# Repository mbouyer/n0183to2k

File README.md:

# n0183to2k
generic NMEA0183 to N2K gateway

This is a generic NMEA0183 to N2K gateway, derived from my weatherstation 
sensor board. It has a NMEA0183 input, switchable 12v power supply output
and a 3.3v i2c connector for additional sensors (e.g. BME280 or SHT20)

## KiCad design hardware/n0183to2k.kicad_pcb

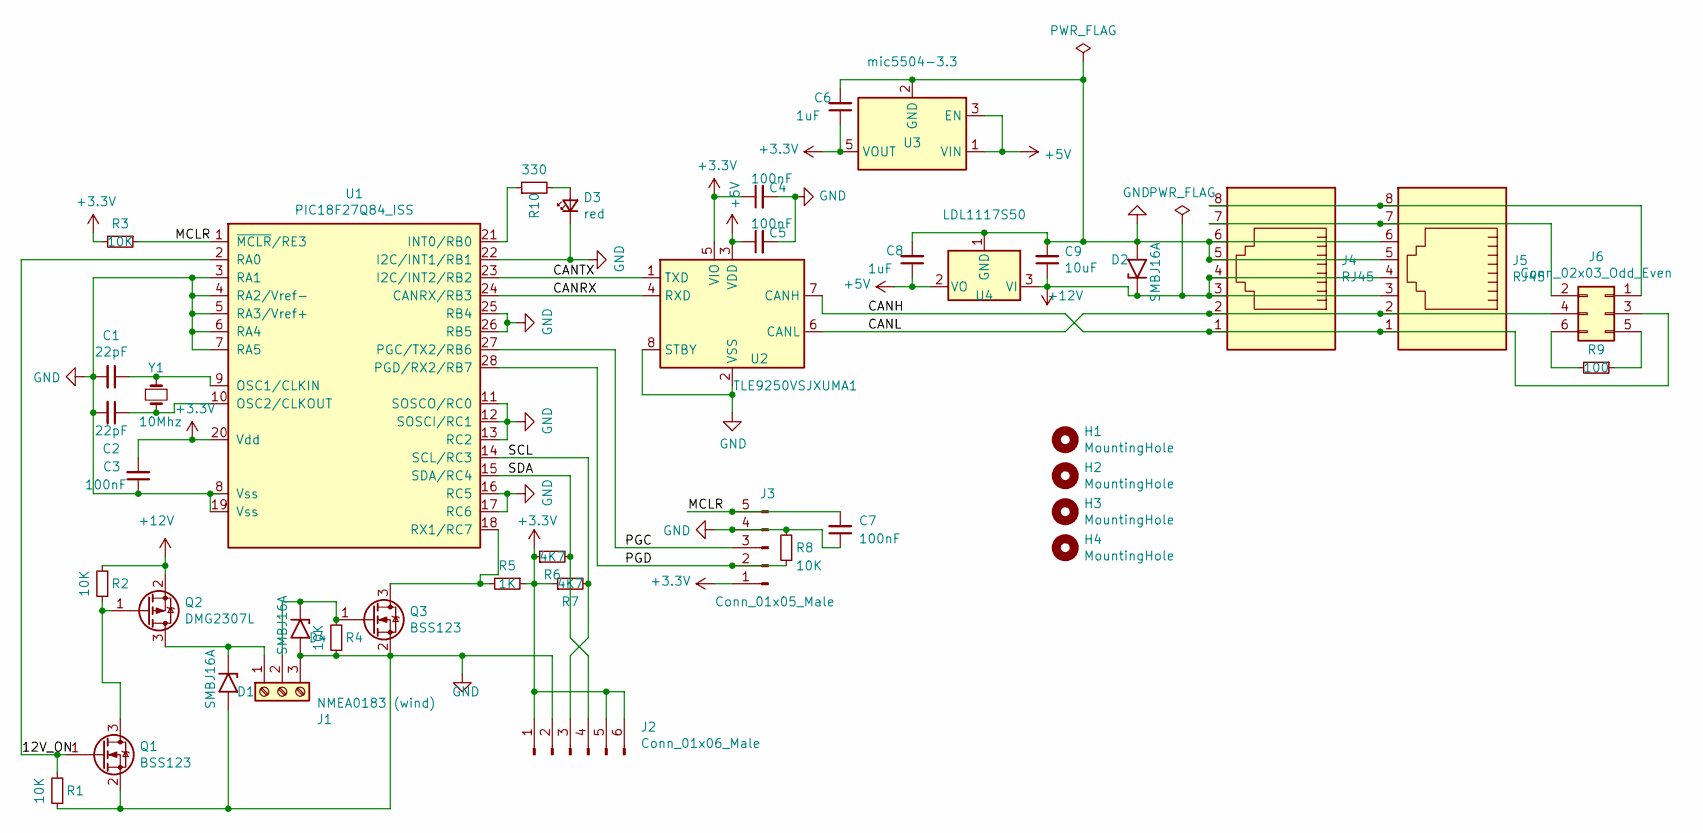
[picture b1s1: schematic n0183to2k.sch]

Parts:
C1, C2: 22pF; C_Disc_D3.8mm_W2.6mm_P2.50mm
C3, C4, C5, C7: 100nF; C_0805_2012Metric_Pad1.18x1.45mm_HandSolder
C6, C8: 1uF; C_0805_2012Metric_Pad1.18x1.45mm_HandSolder
C9: 10uF; C_1210_3225Metric_Pad1.33x2.70mm_HandSolder
D1, D2, D4: SMBJ16A; D_SMB_Handsoldering
D3: red; LED_D3.0mm
H1, H2, H3, H4: MountingHole; MountingHole_3.5mm
J1: NMEA0183 (wind); TerminalBlock_bornier-3_P5.08mm
J2: Conn_01x06_Male; PinHeader_1x06_P2.54mm_Vertical
J3: Conn_01x05_Male; PinHeader_1x05_P2.54mm_Vertical
J4, J5: RJ45; RJ45_Amphenol_54602-x08_Horizontal
J6: Conn_02x03_Odd_Even; PinHeader_2x03_P2.54mm_Vertical
Q1, Q3: BSS123; SOT-23
Q2: DMG2307L; SOT-23
R1, R2, R3, R4, R8: 10K; R_Axial_DIN0207_L6.3mm_D2.5mm_P7.62mm_Horizontal
R5: 1K; R_Axial_DIN0207_L6.3mm_D2.5mm_P7.62mm_Horizontal
R6: 4K7; R_0805_2012Metric_Pad1.20x1.40mm_HandSolder
R7: 4K7; R_Axial_DIN0207_L6.3mm_D2.5mm_P7.62mm_Horizontal
R9: 100; R_0805_2012Metric_Pad1.20x1.40mm_HandSolder
R10: 330; R_Axial_DIN0207_L6.3mm_D2.5mm_P7.62mm_Horizontal
U1: PIC18F27Q84_ISS; SOIC-28W_7.5x17.9mm_P1.27mm
U2: TLE9250VSJXUMA1; SOIC-8_3.9x4.9mm_P1.27mm
U3: mic5504-3.3; SOT-23-5_HandSoldering
U4: LDL1117S50; SOT-223-3_TabPin2
Y1: 10Mhz; Crystal_HC18-U_Vertical

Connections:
+3V3: C3.2, C4.1, C6.1, J2.1, J2.5, J2.6, J3.1, R3.2, R5.1, R6.1, R7.1, U1.20 (Vdd), U2.5 (VIO), U3.5 (VOUT)
+5V: C5.1, C8.1, U2.3 (VDD), U3.1 (VIN), U3.3 (EN), U4.2 (VO)
+12V: C9.1, D2.1 (A1), J4.3, J4.4, J5.3, J5.4, Q2.2 (S), R2.2, U4.3 (VI)
/12V_ON: Q1.1 (G), R1.2, U1.2 (RA0)
/CANH: J4.1, J5.1, J6.3, U2.7 (CANH)
/CANL: J4.2, J5.2, J6.4, U2.6 (CANL)
/CANRX: U1.24 (CANRX/RB3), U2.4 (RXD)
/CANTX: U1.23 (I2C/INT2/RB2), U2.1 (TXD)
/MCLR: C7.2, J3.5, R3.1, U1.1 (~MCLR~/RE3)
/PGC: J3.3, U1.27 (PGC/TX2/RB6)
/PGD: J3.2, R8.1, U1.28 (PGD/RX2/RB7)
/SCL: J2.3, R7.2, U1.14 (SCL/RC3)
/SDA: J2.4, R6.2, U1.15 (SDA/RC4)
GND: C1.2, C2.2, C3.1, C4.2, C5.2, C6.2, C7.1, C8.2, C9.2, D1.2 (A2), D2.2 (A2), D3.1 (K), D4.2 (A2), J1.3, J2.2, J3.4, J4.5, J4.6, J5.5, J5.6, Q1.2 (S), Q3.2 (S), R1.1, R4.1, R8.2, U1.3 (RA1), U1.4 (RA2/Vref-), U1.5 (RA3/Vref+), U1.6 (RA4), U1.7 (RA5), U1.8 (Vss), U1.11 (SOSCO/RC0), U1.12 (SOSCI/RC1), U1.13 (RC2), U1.16 (RC5), U1.17 (RC6), U1.19 (Vss), U1.22 (I2C/INT1/RB1), U1.25 (RB4), U1.26 (RB5), U2.2 (VSS), U2.8 (STBY), U2.9 (VSS), U3.2 (GND), U4.1 (GND)
unnamed: C1.1, U1.9 (OSC1/CLKIN), Y1.1
unnamed: C2.1, U1.10 (OSC2/CLKOUT), Y1.2
unnamed: D1.1 (A1), J1.1, Q2.3 (D)
unnamed: D3.2 (A), R10.2
unnamed: D4.1 (A1), J1.2, Q3.1 (G), R4.2
unnamed: J4.7, J5.7, J6.2
unnamed: J4.8, J5.8, J6.1
unnamed: J6.5, R9.1
unnamed: J6.6, R9.2
unnamed: Q1.3 (D), Q2.1 (G), R2.1
unnamed: Q3.3 (D), R5.2, U1.18 (RX1/RC7)
unnamed: R10.1, U1.21 (INT0/RB0)

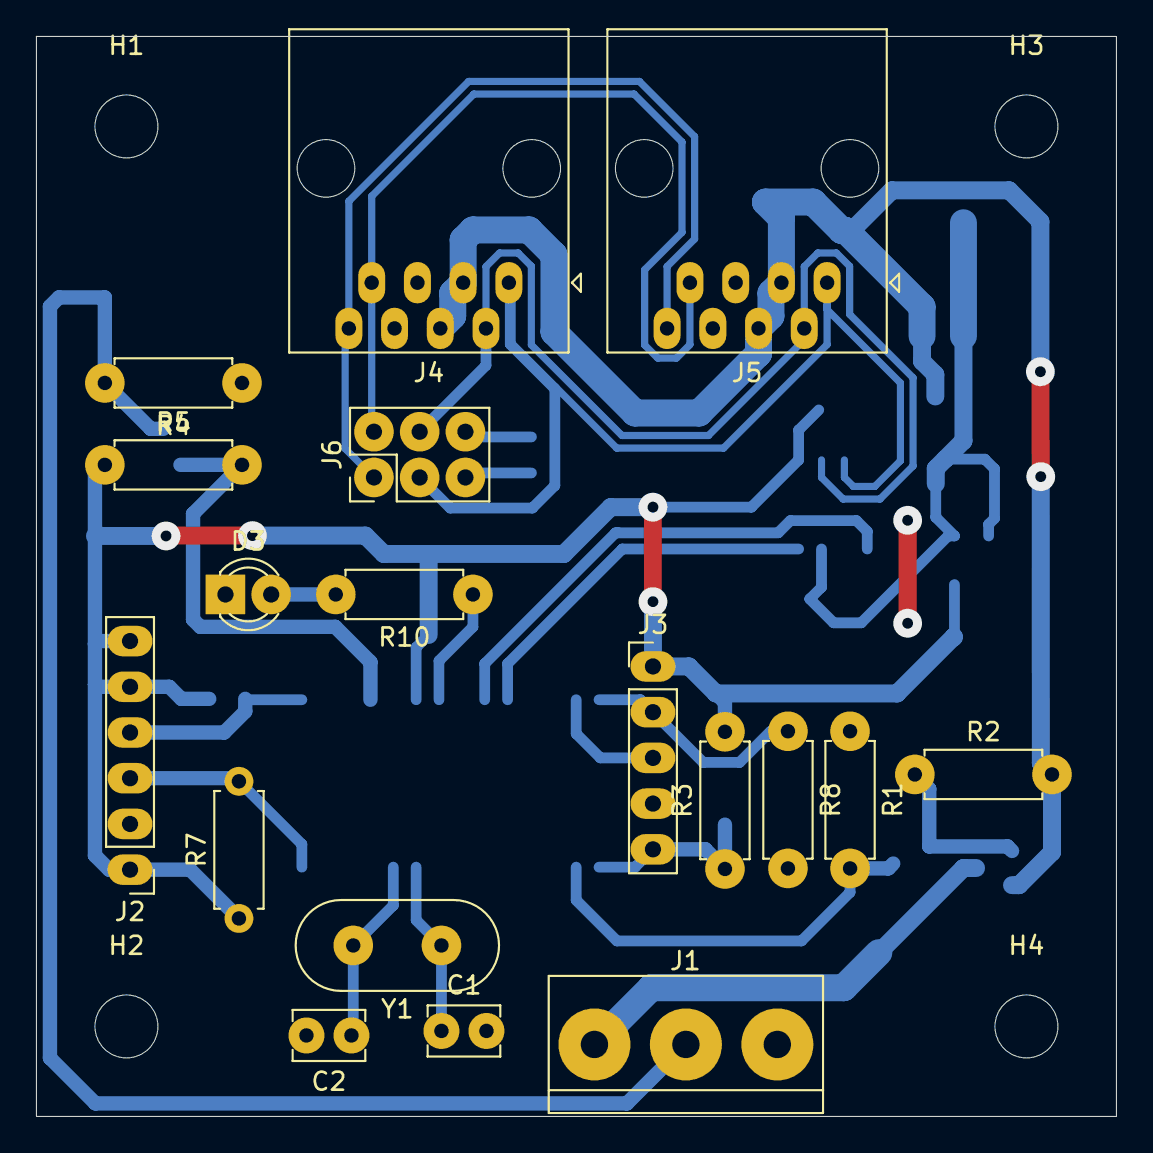
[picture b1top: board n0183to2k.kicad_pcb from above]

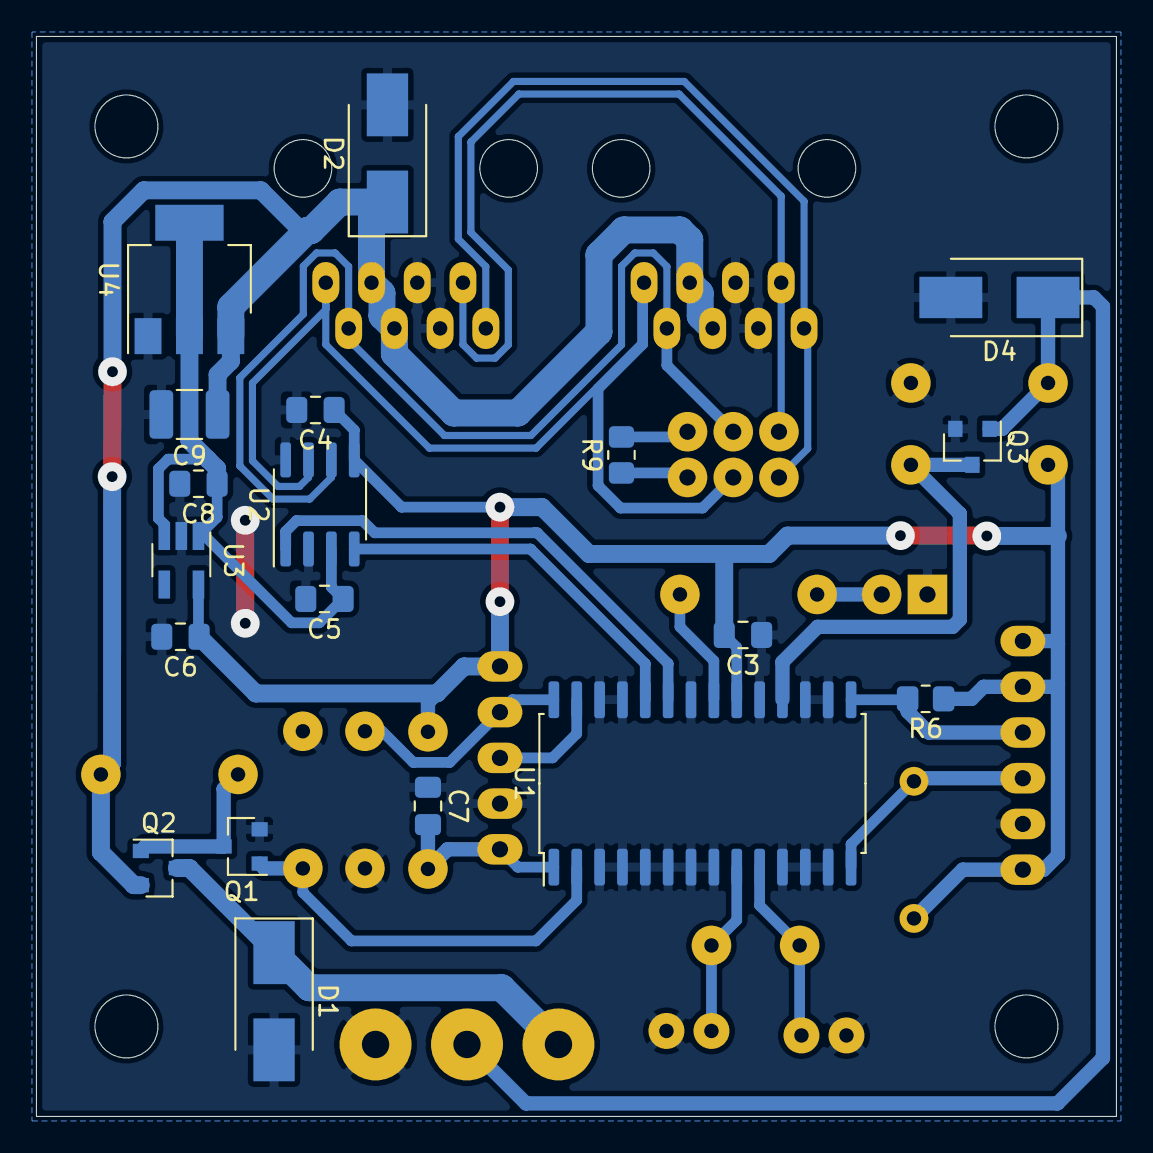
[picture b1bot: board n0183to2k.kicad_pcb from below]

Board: 2 copper layers, 60.0 x 60.0 mm, 41 parts (19 on the bottom side), 26 nets.

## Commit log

2022-03-01 More details
2022-03-03 Add kicad project and schematic.
2022-03-03 Add a LED to a free GPIO.
2022-03-03 Add mounting holes
2022-03-03 Swap LED and resistor for easier routing
2022-03-03 Add a smbj16a on the nmea0183 data line too.
2022-03-03 Annotate
2022-03-03 Work in progress on PCB. Need to check the BME280 module pinout
2022-03-03 properly place the BME280 module connector, and start wriing it.
2022-03-03 move 12V_ON to RA2, closer to the mosfet.
2022-03-03 Complete 3.3v wiring
2022-03-03 replace a SMD resistor with a though-hole to avoid a jumper, and finish routing
2022-03-03 reomve GND nets and add a GND zone
2022-03-05 More strait routing for U4
2022-03-12 Cosmetic fix on a jumper
2022-03-12 move a jumper from a signal trace to GND. Other misc. improvements
2022-03-19 work in progress on software (based on weatherstaion/capteur but adapted for 18f27q84). Enough to build and talk to the bus; n0183 receive not tested; i2c not done.
2022-03-19 U2 on RC7, not U1 turn PWR_ANEMO on
2022-03-19 Make UART2 work
2022-03-19 wind is apparent
2022-03-19 Use LED blinks for status
2022-03-19 handle cambus_mute: if muted, turn power off to anemo, and signal via LED.
2022-03-19 Add the bme280 API from bosh sensortech, Jul 6, 2020 version
2022-03-19 Strip ^M
2022-03-19 API simplification: strip burst register write support.
2022-03-19 Simplifications: remove function pointers
2022-03-19 Assume we do only I2C, all non-needed member now removed from bme280_dev
2022-03-19 remove now unused parameters
2022-03-19 Make it build
2022-03-19 hook bme280 lib
2022-03-19 Switch to 32bit integer math, and fix some warning
2022-03-20 Fix register write
2022-03-20 avoid overflow in delay calculation, use 32 bits.
2022-03-20 Get and send data from the BME280
2022-04-10 Better canbus management
